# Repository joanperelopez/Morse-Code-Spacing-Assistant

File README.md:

# Morse-Code-Spacing-Assistant

## 1. Overview
The **CW Visual Metronome** is a training device designed for radio amateurs practicing Morse code (CW).  
It helps the operator maintain correct **Farnsworth timing** between characters and words by providing **visual cues** through two LEDs.

The device monitors the keyer signal, detects symbol endings, and activates visual indicators at precise intervals derived from the selected **effective WPM** (Words Per Minute).

The system is based on an **Arduino Nano**, with a **1602 LCD display** showing the current speed, a **rotary encoder** for adjustment, and a **memory pushbutton** that stores the selected speed in non-volatile EEPROM memory. 

---

## 2. Functional Description

| Function | Description |
|-----------|--------------|
| **Keyer input** | Detects the Morse key line. When released, timing intervals begin. |
| **Character LED** | Lights up when the inter-character interval (3 dot units) has elapsed since the last key release. |
| **Word LED** | Lights up when the inter-word interval (7 dot units) has elapsed since the last key release. |
| **Rotary encoder** | Adjusts the effective Farnsworth speed (WPM). |
| **LCD display** | Shows the current Farnsworth speed in WPM. |
| **Memory button** | When pressed (active LOW), stores the current speed in EEPROM. |
| **EEPROM memory** | Retains the last stored speed; restored automatically at startup. |

---

## 3. Timing Definition (Farnsworth Method)

The Farnsworth method keeps the character speed constant but lengthens the spacing between characters and words to achieve a slower **effective WPM** for training.

The base time unit (*dot duration*) is calculated as:

Tdot = 1200 / WPM

| Interval | Duration (dot units) | Description |
|-----------|----------------------|--------------|
| Dot (·) | 1 × Tdot | Base unit |
| Dash (–) | 3 × Tdot | Morse standard |
| Intra-character gap | 1 × Tdot | Between elements of a character |
| Inter-character gap | 3 × Tdot | Between two characters |
| Inter-word gap | 7 × Tdot | Between words |

LED indicators:
- **Character LED:** lights after *3 × Tdot* (character spacing).  
- **Word LED:** lights after *7 × Tdot* (word spacing).

---

## 4. User Interface and Operation

1. **Startup**
   - Reads stored speed from EEPROM.
   - Defaults to **15 WPM** if no valid data found.
   - Displays current speed on the LCD.

2. **Adjusting the Speed**
   - Turn the rotary encoder to change the Farnsworth speed.
   - Display updates in real time.

3. **Saving the Speed**
   - Press the *Memory Button* (active LOW) to save current WPM to EEPROM.
   - “Saved in EEPROM” appears briefly on the LCD.

4. **Operating Mode**
   - When the Morse key (active LOW) is pressed, both LEDs turn OFF.
   - After key release:
     - The **Character LED** turns ON after 3 dot units.
     - The **Word LED** turns ON after 7 dot units.
   - When the key is pressed again, both LEDs turn OFF immediately.

---

## 5. Hardware Specifications

| Component | Description |
|------------|--------------|
| **Microcontroller** | Arduino Nano (ATmega328P) |
| **Display** | 1602 alphanumeric LCD |
| **Rotary Encoder** | Incremental (2-channel, mechanical) |
| **EEPROM** | Internal, used for WPM storage |
| **Indicators** | 2 LEDs (character and word) |
| **Memory Button** | Momentary pushbutton, active LOW |
| **Keyer Input** | From key or transceiver, active LOW |
| **Power Supply** | 5 V DC (USB or external) |

---

## 6. Pin Assignments

| Signal | Arduino Pin | Description |
|---------|--------------|-------------|
| **Keyer input** | D2 | Active LOW, internal pull-up |
| **Encoder A** | D3 | Rotary encoder channel A |
| **Encoder B** | D4 | Rotary encoder channel B |
| **LCD D4** | D5 | Data line 4 |
| **LCD D5** | D6 | Data line 5 |
| **LCD RS** | D7 | Register Select |
| **LCD E** | D8 | Enable |
| **LED (character)** | D9 | Character spacing indicator |
| **LED (word)** | D10 | Word spacing indicator |
| **LCD D6** | D11 | Data line 6 |
| **LCD D7** | D12 | Data line 7 |
| **Memory button** | D21 | Active LOW, internal pull-up |

---

## 7. Electrical Characteristics

| Parameter | Typical Value | Notes |
|------------|----------------|-------|
| Supply Voltage | 5 V DC | Standard Arduino Nano |
| Logic HIGH | ≥ 3.0 V | TTL compatible |
| Logic LOW | ≤ 1.0 V | TTL compatible |
| LED Current | 10–15 mA | With 330 Ω series resistors |
| EEPROM Endurance | 100,000 write cycles | Managed via `EEPROM.update()` |

---

## 8. Software Summary

- Language: **C++ (Arduino IDE)**
- Main libraries used:
  - `LiquidCrystal.h` – LCD display control  
  - `RotaryEncoder.h` – rotary encoder handling  
  - `EEPROM.h` – non-volatile memory management
- Main functions:
  - Real-time LED timing based on keyer signal
  - Adjustable Farnsworth WPM
  - EEPROM storage of configuration
  - LCD visual feedback

---

## 9. Default Parameters

| Parameter | Default Value | Range |
|------------|----------------|--------|
| **Farnsworth speed** | 15 WPM | 5–40 WPM |
| **Character spacing** | 3 × Tdot | — |
| **Word spacing** | 7 × Tdot | — |

---

TOP view of the circuit

BOTTOM view of the circuit

3D Model of the plastic cover

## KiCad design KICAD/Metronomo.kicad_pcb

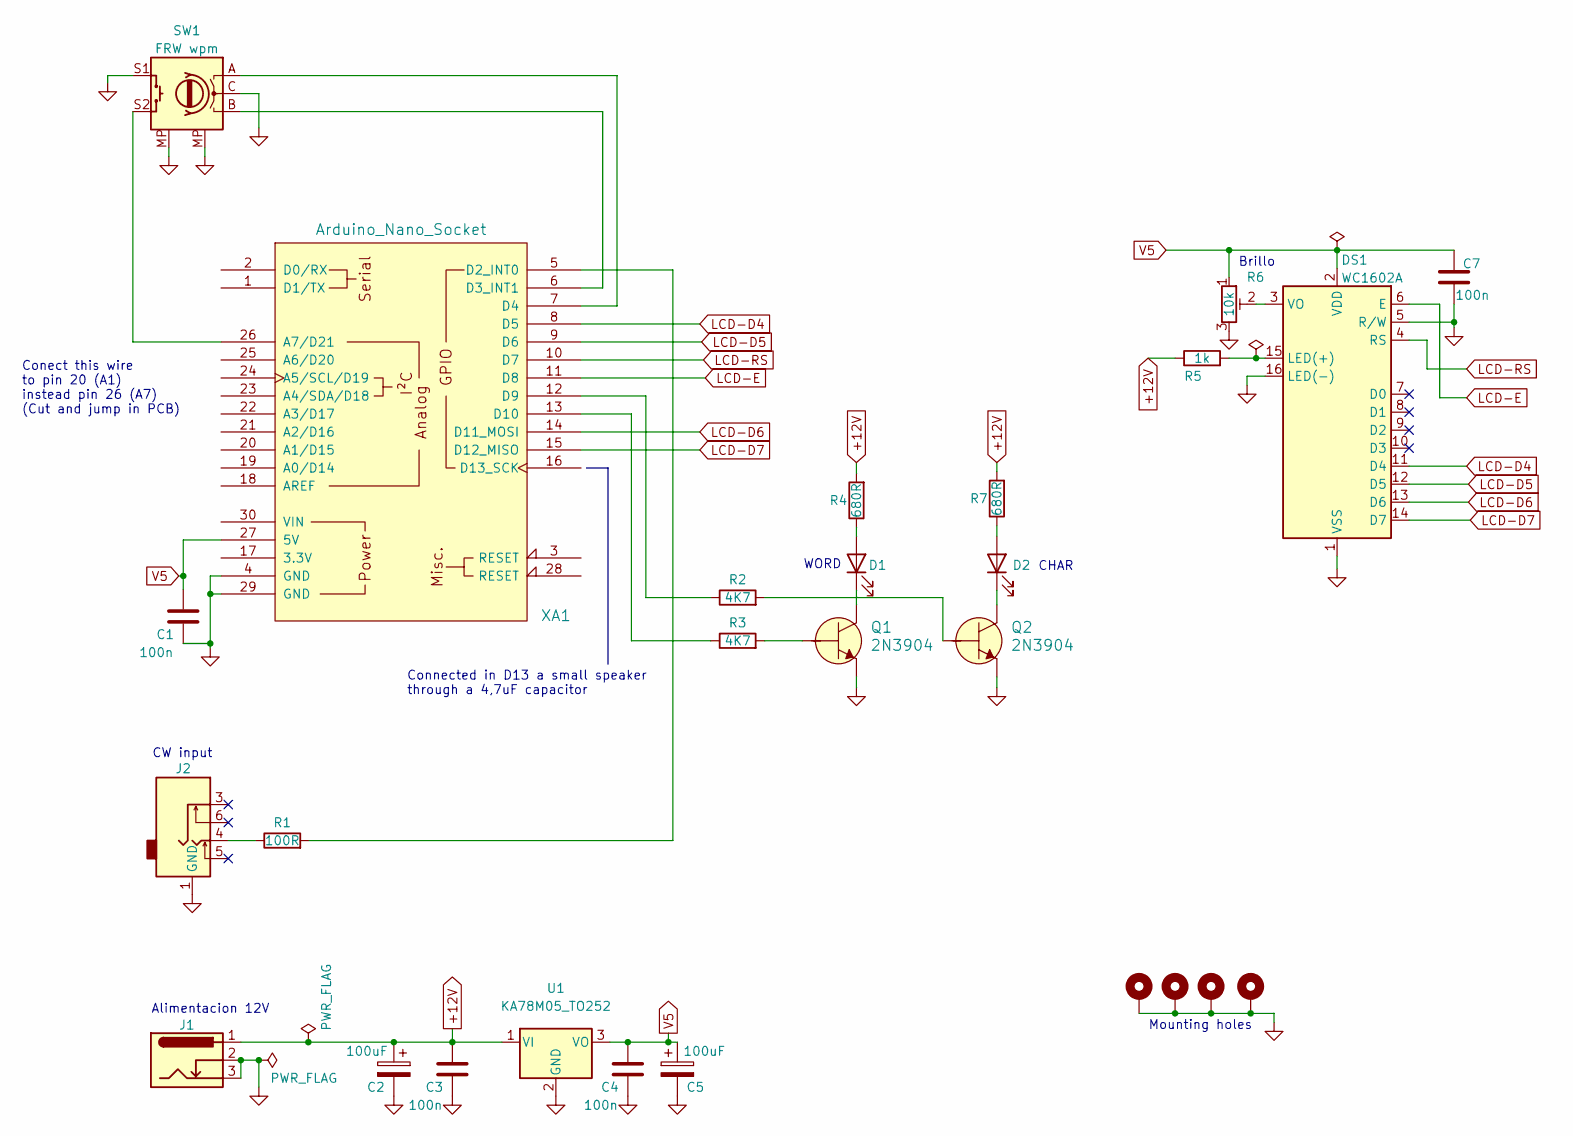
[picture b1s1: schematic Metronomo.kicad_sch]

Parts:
C1, C3, C4, C7: 100n; C_0805_2012Metric
C2, C5: 100uF; C_Elec_8x10.2
D1, D2: LED; LED_D5.0mm
DS1: WC1602A
H1, H2, H3, H4: MountingHole_Pad; MountingHole_3.2mm_M3_Pad_TopBottom
J1: Barrel_Jack_Switch_Pin3Ring; BarrelJack_GCT_DCJ200-10-A_Horizontal
J2: AudioJack4_PERE; AUDIO-JACK4
Q1, Q2: 2N3904; SOT23-3; MPN 2N3904; Digi-Key_PN 2N3904CS-ND
R1: 100R; R_0805_2012Metric_Pad1.20x1.40mm_HandSolder
R2, R3: 4K7; R_0805_2012Metric_Pad1.20x1.40mm_HandSolder
R4, R7: 680R; R_0805_2012Metric_Pad1.20x1.40mm_HandSolder
R5: 1k; R_0805_2012Metric_Pad1.20x1.40mm_HandSolder
R6: 10k; Potentiometer_Piher_PT-10-V10_Vertical
SW1: FRW wpm; RotaryEncoder_Alps_EC11E_Vertical_H20mm
U1: KA78M05_TO252; TO-252
XA1: Arduino_Nano_Socket; Arduino_Nano

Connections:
+12V: C2.1, C3.2, J1.1, R4.2, R5.1, R7.2, U1.1 (VI)
GND: C1.1, C2.2, C3.1, C4.1, C5.2, C7.1, DS1.1 (VSS), DS1.5 (R/W), DS1.16 (LED(-)), H1.1, H2.1, H3.1, H4.1, J1.2, J1.3, J2.1 (GND), Q1.2 (E), Q2.2 (E), R6.3, SW1.C, SW1.MP, SW1.S1, U1.2 (GND), XA1.4 (GND), XA1.29 (GND)
LCD-D4: DS1.11 (D4), XA1.8 (D5)
LCD-D5: DS1.12 (D5), XA1.9 (D6)
LCD-D6: DS1.13 (D6), XA1.14 (D11_MOSI)
LCD-D7: DS1.14 (D7), XA1.15 (D12_MISO)
LCD-E: DS1.6 (E), XA1.11 (D8)
LCD-RS: DS1.4 (RS), XA1.10 (D7)
unnamed: D1.2 (A), R4.1
unnamed: D1.1 (K), Q1.3 (C)
unnamed: D2.2 (A), R7.1
unnamed: D2.1 (K), Q2.3 (C)
unnamed: DS1.15 (LED(+)), R5.2
unnamed: DS1.3 (VO), R6.2
unnamed: J2.4, R1.1
unnamed: Q1.1 (B), R3.2
unnamed: Q2.1 (B), R2.2
unnamed: SW1.S2, XA1.26 (A7/D21)
unnamed: R1.2, XA1.5 (D2_INT0)
unnamed: SW1.B, XA1.6 (D3_INT1)
unnamed: SW1.A, XA1.7 (D4)
unnamed: R2.1, XA1.12 (D9)
unnamed: R3.1, XA1.13 (D10)
V5: C1.2, C4.2, C5.1, C7.2, DS1.2 (VDD), R6.1, U1.3 (VO), XA1.27 (5V)

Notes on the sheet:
Mounting holes
Connected in D13 a small speaker through a 4,7uF capacitor
Alimentacion 12V
CW input
CHAR
WORD
Conect this wire to pin 20 (A1) instead pin 26 (A7) (Cut and jump in PCB)
Brillo

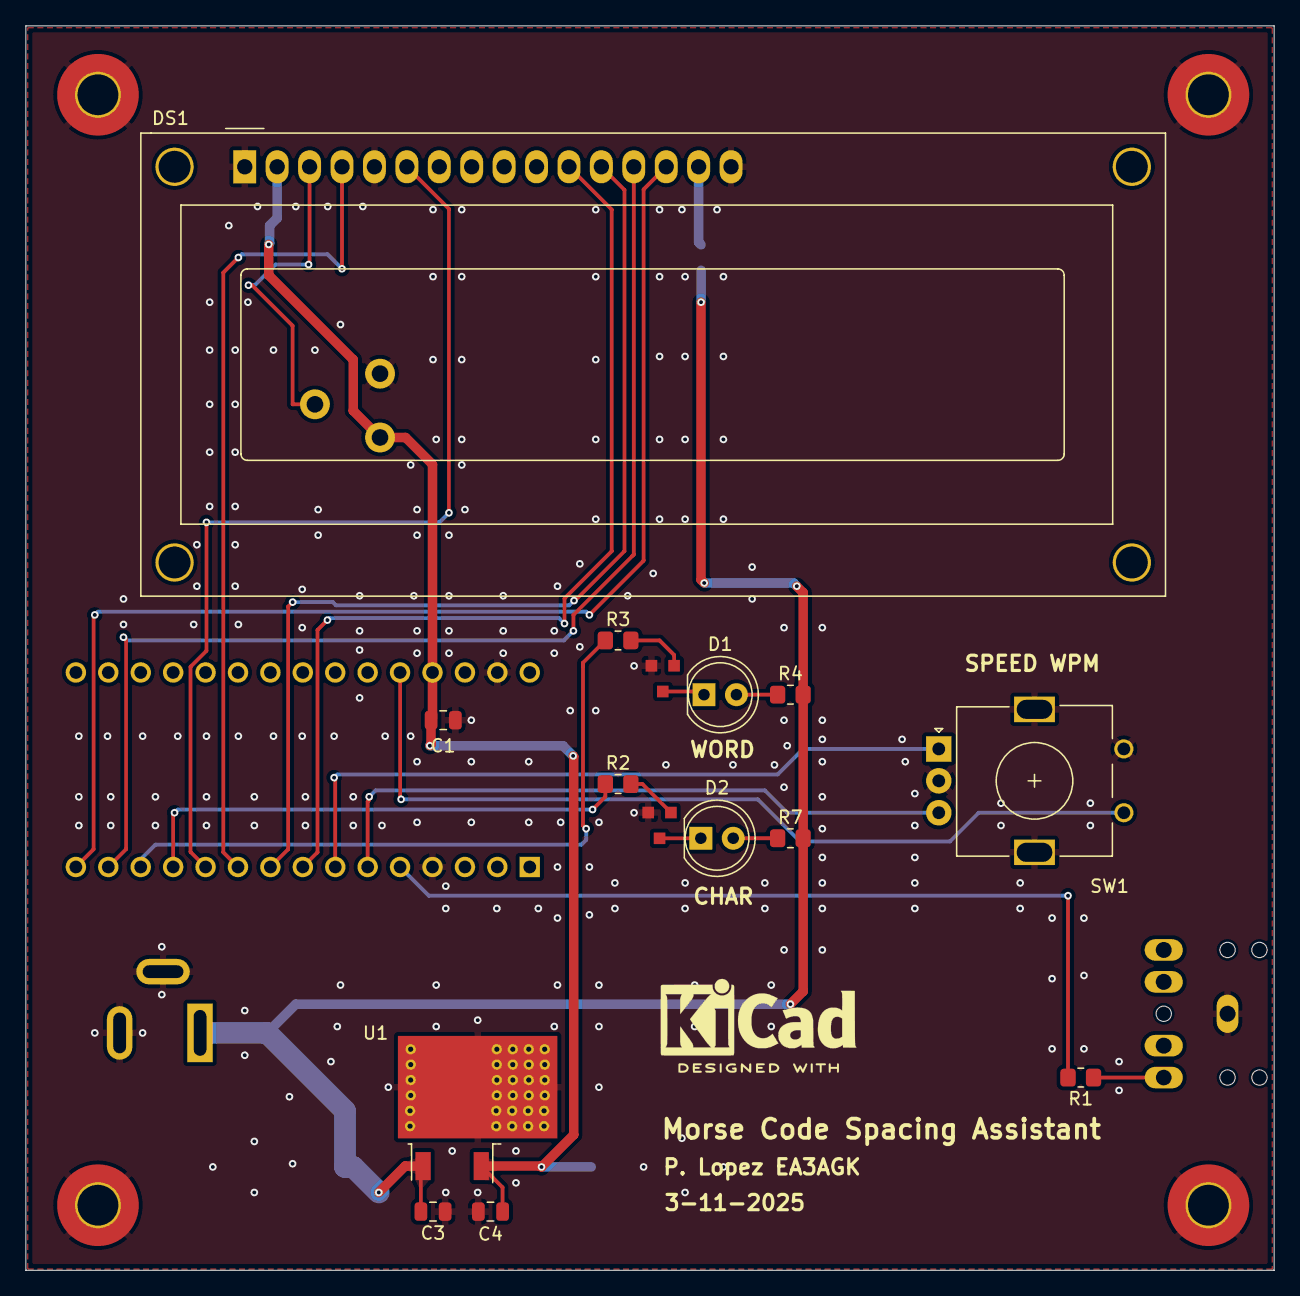
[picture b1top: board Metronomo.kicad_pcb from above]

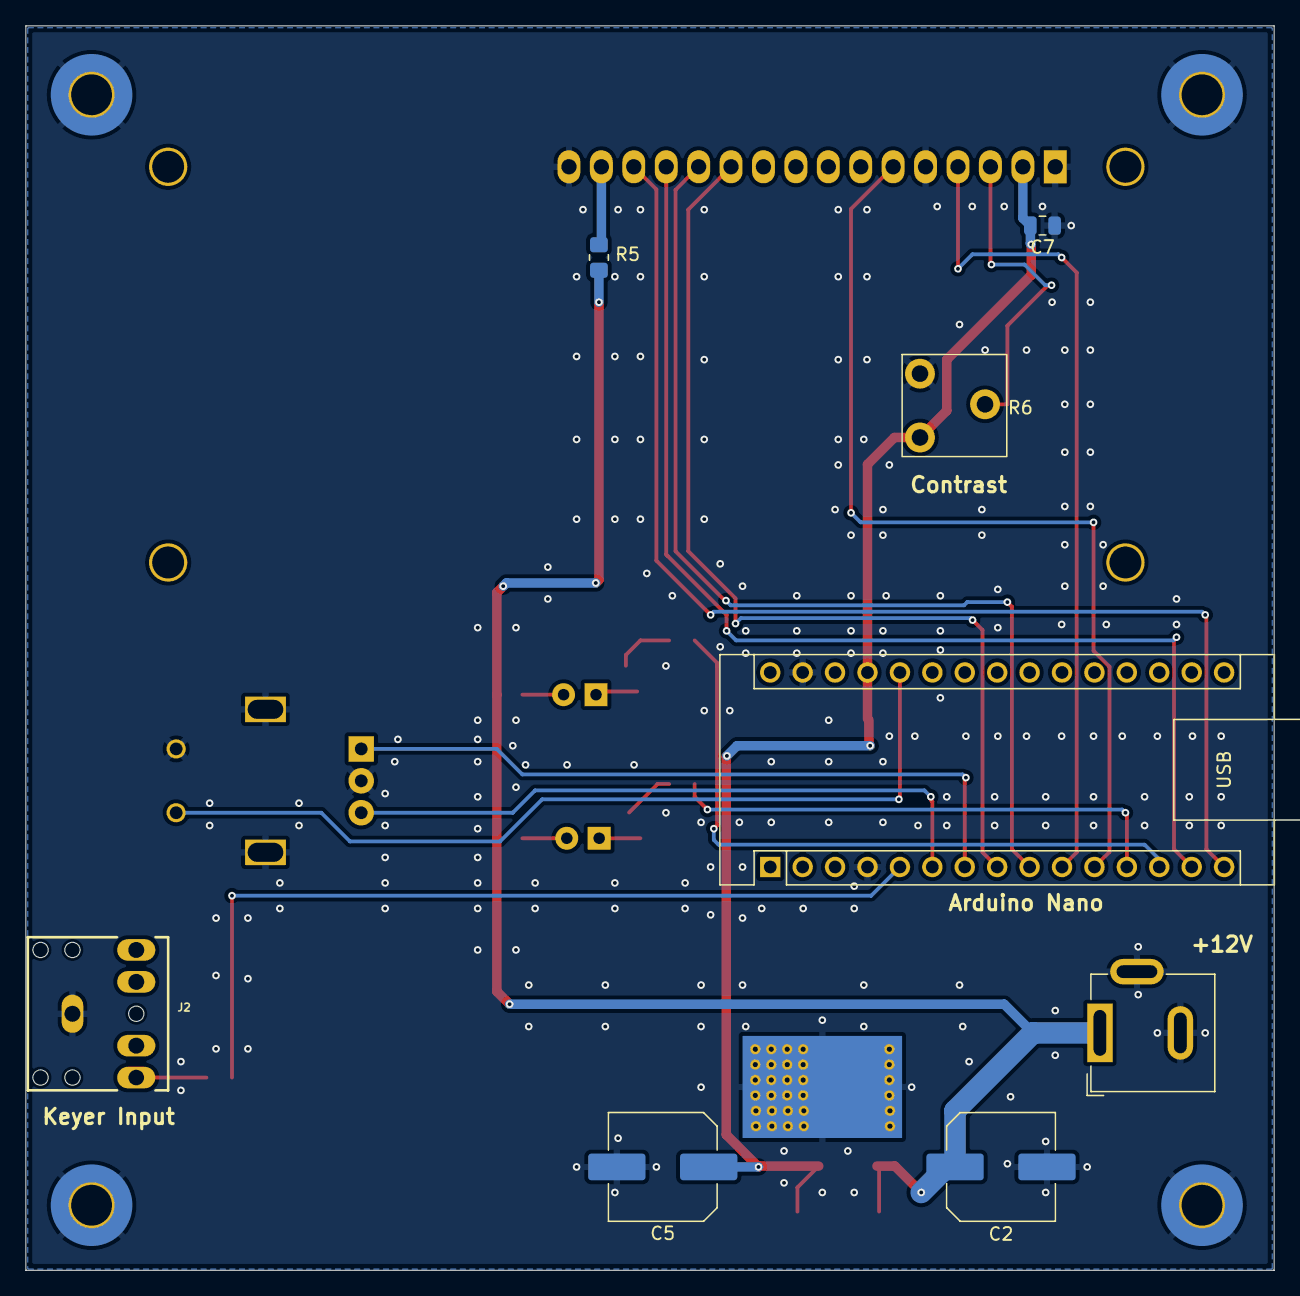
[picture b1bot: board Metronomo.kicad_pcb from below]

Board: 2 copper layers, 97.8 x 97.5 mm, 27 parts (8 on the bottom side), 24 nets.

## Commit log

2025-11-03 Enhance README with Farnsworth spacing details
    Added explanation of Farnsworth spacing in Morse code.
2025-11-03 Add images for visual representation
    Added images to enhance the README content.
2025-11-03 Enhance README with comprehensive device details
    Expanded the README with detailed sections on user interface, hardware specifications, electrical characteristics, software summary, default parameters, and author information.
2025-11-03 Fix formatting issue in README.md
2025-11-03 Fix formatting in README.md for Morse code table
2025-11-03 Update README to remove author and add circuit images
    Removed author section and added images of the circuit.
2025-11-03 Create none
2025-11-03 Create
2025-11-03 Add 'gg' to SOFTWARE file
2025-11-12 Add 3D model image to README
2025-11-18 Add note about software modifications
2025-11-18 Revise README with version V2.1 details
    Updated README to include versioning and hardware modifications.
2025-11-18 Fix formatting and typos in README.md
    Correct formatting and spelling in README.
2025-11-18 Change version from V2.1 to V2.2
    Updated version number and corrected spelling.
2025-12-04 Add images to README for enhanced visualization
    Added additional images to the README for better visualization.
